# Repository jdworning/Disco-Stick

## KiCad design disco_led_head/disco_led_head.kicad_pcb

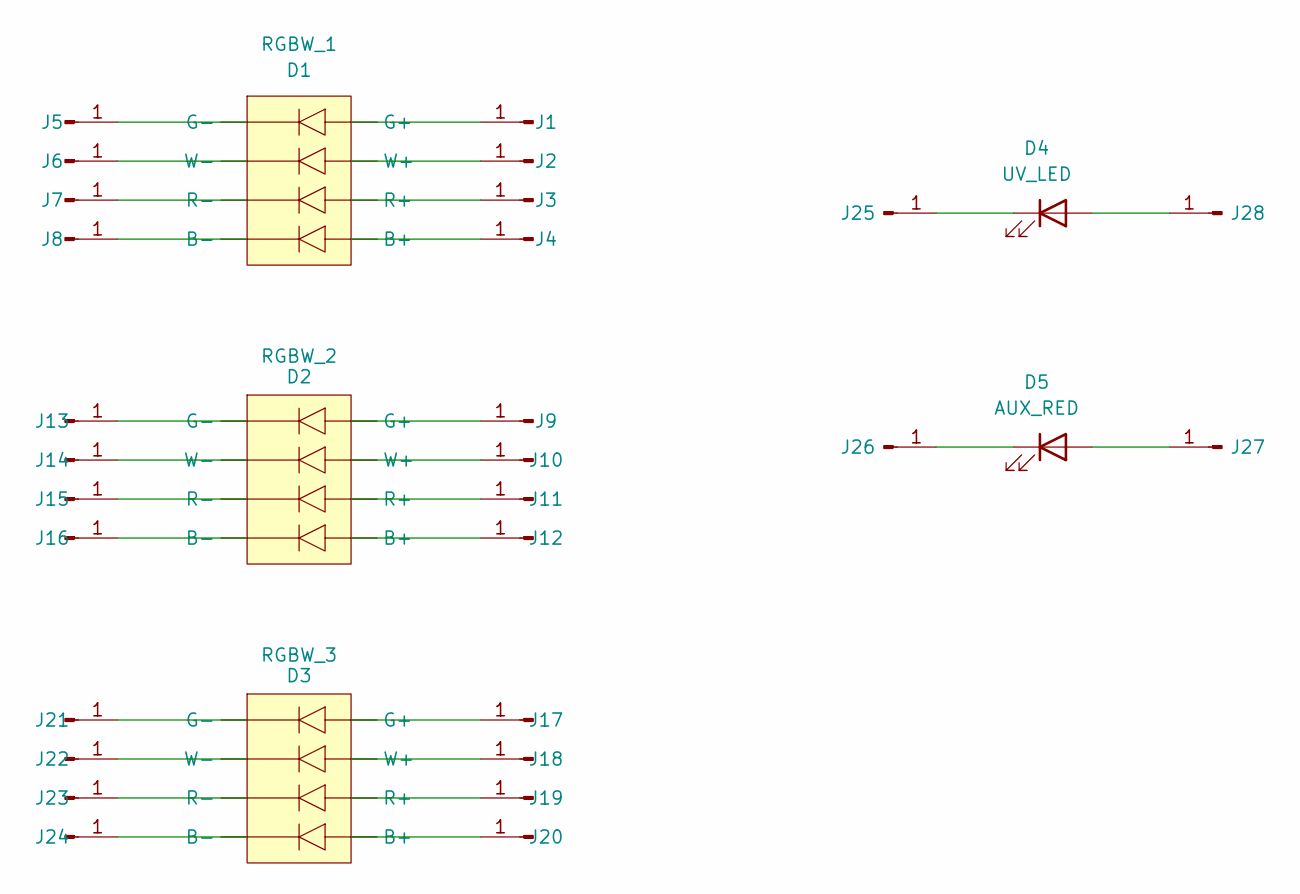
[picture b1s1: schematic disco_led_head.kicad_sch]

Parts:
D1: RGBW_1; LED_SOIC_RGBW
D2: RGBW_2; LED_SOIC_RGBW
D3: RGBW_3; LED_SOIC_RGBW
D4: UV_LED; Red_LED_5W
D5: AUX_RED; Red_LED_5W
J1: G1+; LED_Pad
J2: W1+; LED_Pad
J3: R1+; LED_Pad
J4: B1+; LED_Pad
J5: G1-; LED_Pad
J6: W1-; LED_Pad
J7: R1-; LED_Pad
J8: B1-; LED_Pad
J9: G2+; LED_Pad
J10: W2+; LED_Pad
J11: R2+; LED_Pad
J12: B2+; LED_Pad
J13: G2-; LED_Pad
J14: W2-; LED_Pad
J15: R2-; LED_Pad
J16: B2-; LED_Pad
J17: G3+; LED_Pad
J18: W3+; LED_Pad
J19: R3+; LED_Pad
J20: B3+; LED_Pad
J21: G3-; LED_Pad
J22: W3-; LED_Pad
J23: R3-; LED_Pad
J24: B3-; LED_Pad
J25: UV-; LED_Pad
J26: A_R-; LED_Pad
J27: A_R+; LED_Pad
J28: UV+; LED_Pad

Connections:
unnamed: D1.4 (B+), J4.1
unnamed: D1.8 (B-), J8.1
unnamed: D1.1 (G+), J1.1
unnamed: D1.5 (G-), J5.1
unnamed: D1.3 (R+), J3.1
unnamed: D1.7 (R-), J7.1
unnamed: D1.2 (W+), J2.1
unnamed: D1.6 (W-), J6.1
unnamed: D2.4 (B+), J12.1
unnamed: D2.8 (B-), J16.1
unnamed: D2.1 (G+), J9.1
unnamed: D2.5 (G-), J13.1
unnamed: D2.3 (R+), J11.1
unnamed: D2.7 (R-), J15.1
unnamed: D2.2 (W+), J10.1
unnamed: D2.6 (W-), J14.1
unnamed: D3.4 (B+), J20.1
unnamed: D3.8 (B-), J24.1
unnamed: D3.1 (G+), J17.1
unnamed: D3.5 (G-), J21.1
unnamed: D3.3 (R+), J19.1
unnamed: D3.7 (R-), J23.1
unnamed: D3.2 (W+), J18.1
unnamed: D3.6 (W-), J22.1
unnamed: D4.2 (A), J28.1
unnamed: D4.1 (K), J25.1
unnamed: D5.2 (A), J27.1
unnamed: D5.1 (K), J26.1

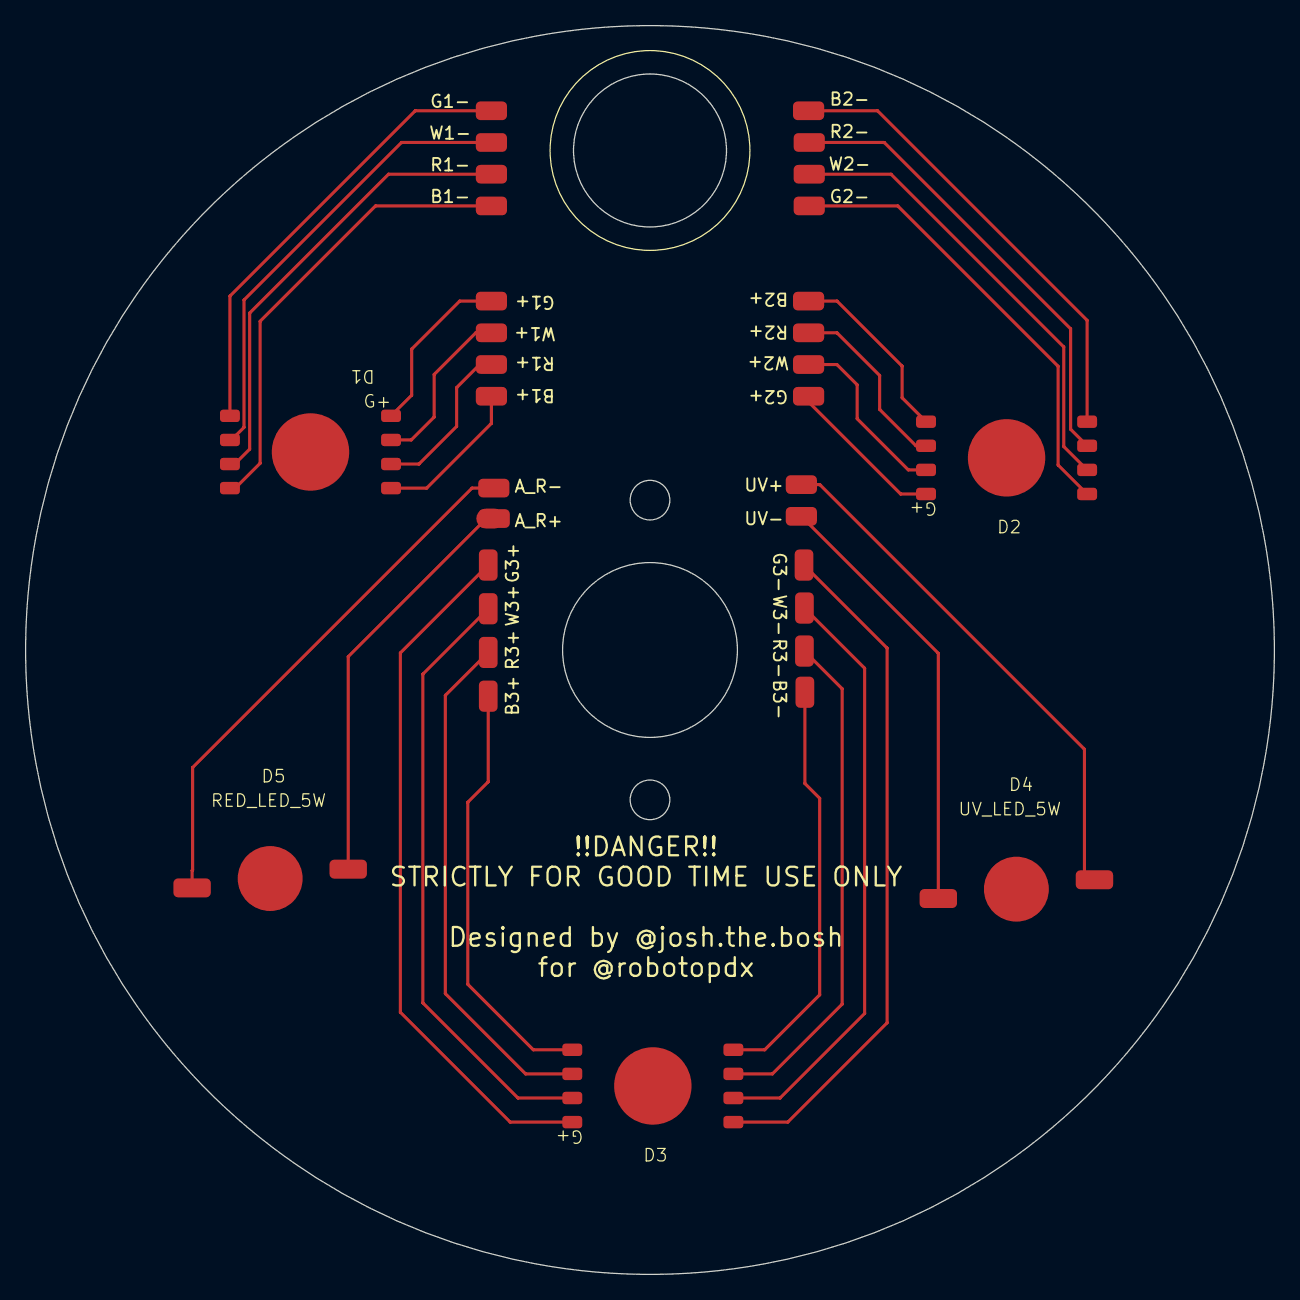
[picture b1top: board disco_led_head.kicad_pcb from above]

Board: 2 copper layers, 100.0 x 100.0 mm, 33 parts (0 on the bottom side), 28 nets.

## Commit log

2024-03-21 Reorganized folders
2024-03-21 Updated files and moved some around
    Final update to schematic
    Created layout and schematic printout.
    Compiled fabrication files into zip file.
2024-03-25 Update to PCB Footprints
2024-03-25 Small Update
